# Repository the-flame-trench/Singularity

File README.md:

# Singularity On-board Computer
Singularity is a high-reliability focused on-board computer (OBC) for Pocketqube scale spacecraft.

It has been designed with a high degree of redundancy and fault tolerance in mind, and is compliant to ECSS-Q-ST-70-12C where possible.

# Design
The computer is based on the TI TMS570 family of safety critical microcontrollers, utilising dual lockstep ARM Cortex R4F CPU cores with extensive error checking capabilies.  

The rest of the board contains 8Mb external FRAM, 1Gb external bulk flash (both on their own single SPI bus), and a supervisor IC with RTC, watchdog and 256kb integrated FRAM (Issue_PROTO_A only).

Additionally, the board breaks out 3 CAN buses, with 1 designated for platform services, 1 for payload use, and a shared redundant bus.

As the Singularity OBC is being designed primarily for use in our TFTqube project, specific functions have been broken out to each connector, including a UART bus to a GPS module and a shared internal/external I2C bus.

The board is designed to be powered by a 3V3 external supply.  For maximum reliability, this supply should have some level of redundancy.  There is also a designated 5V input rail, although this is currently unused.

The board contains bulk decoupling for the main 3V3 rail, which is then distributed to various ICs.  The 3V3 rail is also fed through redundant TPS62850 switch mode power supplies, with outputs OR'd by an ideal diode controller and pair of MOSFETS, to provide a redundant 1V2 rail for the TMS570 core supply.

A version of the computer with 32MB SDRAM is under study, however at present, on an already dense 6 layer board, layout is infeasible.

# Usage
First, clone [TFT-KiCad-Source](https://github.com/the-flame-trench/TFT-KiCad-Source) and import all symbol and footprint libraries, found under /TFT_symbols and /TFT_footprints respectively, to your KiCad installation.  This MUST be done first, as the Singularity project references this library (as do other TFT projects).

Then, clone the Singularity repo, ensuring that your library tables are correctly set up with the TFT component libraries before opening the project.

# Contributing
The schematic and PCB are being designed in KiCad v6.0, and will move with the latest stable version.

We are working to bring every symbol and footprint into the TFT KiCad source libraries, however currently there are still a few instances using the default KiCad component library.

# Licence
Licenced under the [CERN OHLv2 - Strongly Reciprocal](LICENCE) or as referenced.

(c) The Flame Trench 2022

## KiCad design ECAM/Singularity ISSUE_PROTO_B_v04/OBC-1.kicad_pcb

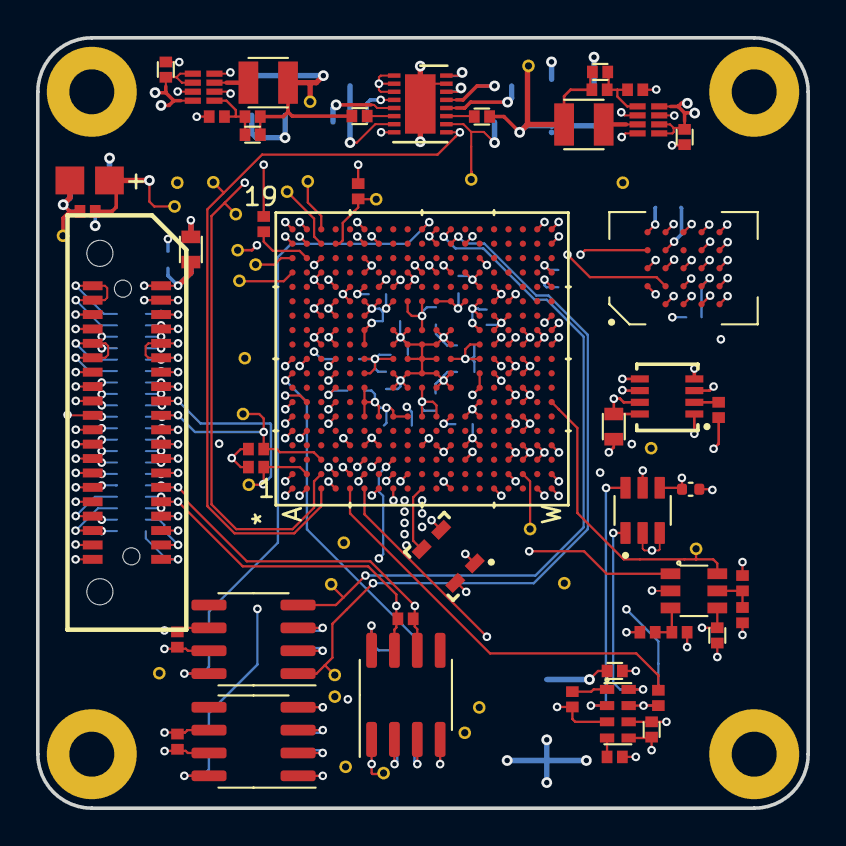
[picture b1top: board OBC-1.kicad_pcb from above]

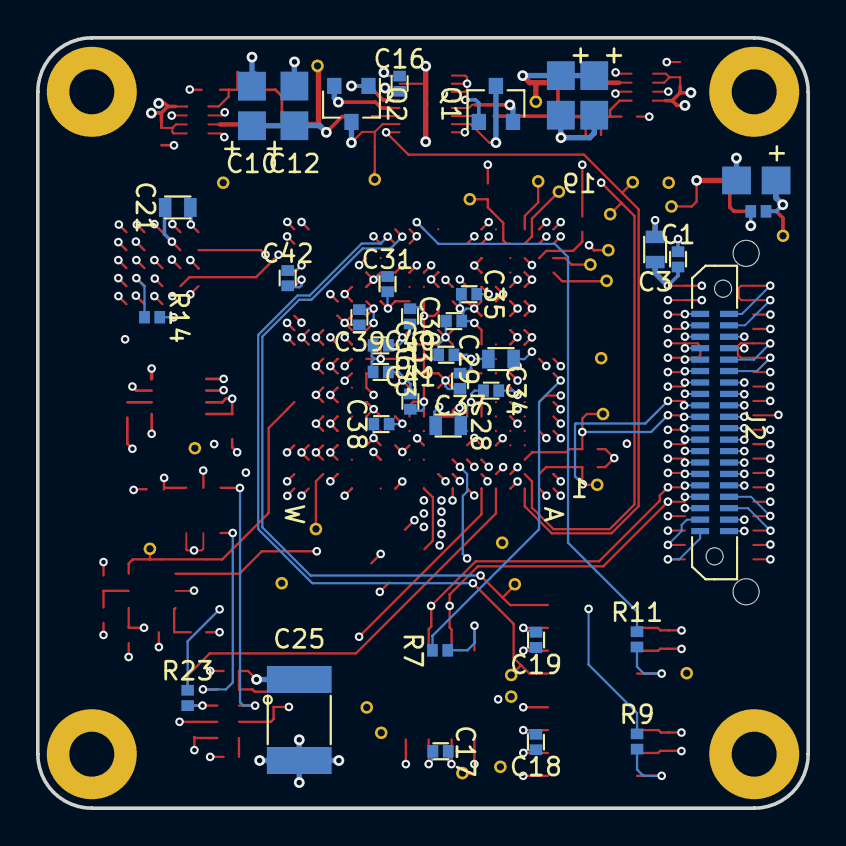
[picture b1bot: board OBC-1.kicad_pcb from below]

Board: 6 copper layers, 42.8 x 42.8 mm, 121 parts (37 on the bottom side), 76 nets.

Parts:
C1, C6, C7, C16, C17, C18, C19, C22, C23, C24, C30, C31, C32, C33, C34, C35, C36, C37, C38, C39, C40, C41, C42: 100n-10V-0402-5%-CER; 0402_CAP
C2, C3, C28, C29: 1u-10V-0603-10%-CER; 0603_CAP
C4, C5: 10u-10V-1206-10%-TANT; 1206_CAP_TANT
C8, C9: 10p-50V-0402-0.5p-CER; 0402_CAP
C10, C11, C12, C13: 10u-10V-0603-10%-CER; 1206_CAP_TANT
C14, C15: 56n-16V-0402-10%-CER; 0402_CAP
C20, C21: 100n-10V-0402-5%-CER; 0603_CAP
C25: 100uAH-1V8-4.4x3mm_LIon_batt; 1812_BATT
C26: 10n-10V-0402-5%-CER; C_0402_1005Metric
H1, H2, H3, H4: MountingHole_Pad; MountingHole_2.5mm_Pad
J1: ERM8-020-X; ERM8-020-XX.X-X-DV
J2: ERF6-020-X; ERF6-020-XX.X-X-DV-A-XX-K
L1, L2: 470nH-4A-20%; 2.5x2mm_I_SMD
Q1, Q2: MGSF1N02L; SOT-23
R1, R2: 100K-50V-0402-1%; 0402_RES
R3, R5: 16K2-50V-0402-1%; 0402_RES
R4, R6: 15K-50V-0402-1%; 0402_RES
R7, R9, R11, R25, R26: 10K-50V-0402-1%; 0402_RES
R8, R10, R12: 120R-50V-0402-1%; 0402_RES
R13, R14: 39R0-50V-0402-1%; 0402_RES
R15, R16, R21, R22, R23, R24: 0R-50V-0402; 0402_RES
R17, R18, R19, R20: 4K7-50V-0402-1%; 0402_RES
TP1, TP2, TP3, TP4, TP5, TP6, TP7, TP8, TP9, TP10, TP11, TP12, TP13, TP14, TP15, TP16, TP17, TP18, TP19, TP20, TP21, TP22, TP23, TP24, TP25, TP26, TP27, TP28, TP29, TP36, TP37: TEST-POINT; TP_0.4mmholesize_0.3mmring
U1, U2: TPS62850x-Q1; SOT-583
U3: LTC4353; DFN-16-1EP_3x4mm_P0.45mm_EP1.7x3.3mm
U4, U5, U6: SN65HVD230M-EP; SOIC-8_3.9x4.9mm_P1.27mm
U7: CY15B108QI
U8: S70FL01GS; BGA-24_5x5_6.0x8.0mm
U9: TPS3813K33-EP; SOT-236
U10: RV-3032-C7
U11: TMS5701227CZWTQQ1; ZWT337
U12: TMP100; SOT-23
X2: LFTCXO075797

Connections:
/CAN_XCVR_PL/CAN_H_PL: J1.16, R8.1, U4.7
/CAN_XCVR_PL/CAN_L_PL: J1.15, R8.2, U4.6
/CAN_XCVR_PL/CAN_PL_D: TP22.1, U4.1, U11.A10
/CAN_XCVR_PL/CAN_PL_R: TP24.1, U4.4, U11.B10
/CAN_XCVR_PL/CAN_PL_Rs: R7.1, U11.A9
/CAN_XCVR_R/CAN_H_PL: J1.19, J2.19, R10.1, U5.7
/CAN_XCVR_R/CAN_L_PL: J1.20, J2.20, R10.2, U5.6
/CAN_XCVR_R/CAN_PL_D: TP21.1, U5.1, U11.H2
/CAN_XCVR_R/CAN_PL_R: TP20.1, U5.4, U11.H1
/CAN_XCVR_R/CAN_PL_Rs: R9.1, U11.G1
/Connectors/ADS_nRST: J1.11, U11.M1
/Connectors/CAN_H_PA: J1.24, J2.24, R12.1, U6.7
/Connectors/CAN_L_PA: J1.23, J2.23, R12.2, U6.6
/Connectors/GPS_P1PPS: J1.29, U11.A6
/Connectors/GPS_RXD0: J1.31, U11.B7
/Connectors/GPS_STS: J1.28, U11.A5
/Connectors/GPS_TXD0: J1.32, U11.A7
/Connectors/GPS_nRST: J1.30, U11.B5
/FL_1/FL_1_CLK: U8.B2, U11.F18
/FL_1/FL_1_SI_IO0: U8.D3, U11.F19
/FL_1/FL_1_SO_IO1: R14.1, U11.G18
/FL_1/FL_1_nCS1: U8.C2, U11.F3
/FL_1/FL_1_nCS2: U8.A3, U11.G3
/FL_1/FL_1_nHOLD_IO3: U8.D4, U11.H3
/FL_1/FL_1_nRESET: U8.A4, U11.F2
/FRAM_1/FRAM_1_CIPO: R13.1, U11.D2
/FRAM_1/FRAM_1_CLK: U7.6, U11.E2
/FRAM_1/FRAM_1_COPI: U7.5, U11.D1
/FRAM_1/FRAM_1_nCS: U7.1, U11.N3
/Power/GATE_1: Q2.2, U3.12
/Power/GATE_2: Q1.2, U3.5
/Power/OBC_1V25_P_PG: TP36.1, U3.9, U11.C1
/Power/OBC_1V25_R_PG: TP37.1, U3.8, U11.C2
/RTC/OBC_I2C_SCL: J1.10, R20.2, TP29.1, U10.8, U11.C3, U12.1
/RTC/OBC_I2C_SDA: J1.9, R19.2, TP28.1, U10.2, U11.B2, U12.6
/RTC/RTC_CLKOUT: R23.2, R24.2, U10.7
/RTC/RTC_nINT: R26.2, U10.3, U11.F1
/Supervisor/SPVSR_PET: U9.1, U11.J2
/Supervisor/SPVSR_nRST: TP27.1, U9.6, U11.W7
/Supervisor/WDR: R21.2, R22.1, U9.5
/Supervisor/WDT: R15.2, R16.1, U9.3
/TMS570_uC/CAN_PA_D: TP25.1, U6.1, U11.M18
/TMS570_uC/CAN_PA_R: TP23.1, U6.4, U11.M19
/TMS570_uC/CAN_PA_Rs: R11.1, U11.K19
/TMS570_uC/JTAG_RTCK: TP1.1, U11.A16
/TMS570_uC/JTAG_TCK: TP5.1, U11.B18
/TMS570_uC/JTAG_TDI: TP2.1, U11.A17
/TMS570_uC/JTAG_TDO: TP6.1, U11.C18
/TMS570_uC/JTAG_TEST: TP3.1, U11.U2
/TMS570_uC/JTAG_TMS: TP7.1, U11.C19
/TMS570_uC/JTAG_nTRST: R17.1, TP4.1, U11.D18
/TMS570_uC/uC_OSC_IN: U11.K1, X2.3
/TMS570_uC/uC_nRST: R18.1, U11.B17
GND: C1.2, C2.2, C3.2, C5.2, C6.2, C7.2, C10.2, C11.2, C12.2, C13.2, C16.2, C17.2, C18.2, C19.2, C20.2, C21.2, C22.2, C23.2, C24.2, C25.2, C26.2, C28.2, C29.2, C30.2, C31.2, C32.2, C33.2, C34.2, C35.2, C36.2, C37.2, C38.2, C39.2, C40.2, C41.2, C42.2, H1.1, H2.1, H3.1, H4.1, J1.3, J1.4, J1.5, J1.6, J1.7, J1.8, J1.12, J1.13, J1.14, J1.17, J1.18, J1.21, J1.22, J1.25, J1.26, J1.27, J1.33, J1.34, J1.37, J1.38, J2.1, J2.2, J2.3, J2.4, J2.5, J2.6, J2.7, J2.8, J2.9, J2.10, J2.11, J2.12, J2.13, J2.14, J2.15, J2.16, J2.17, J2.18, J2.21, J2.22, J2.25, J2.26, J2.27, J2.28, J2.29, J2.30, J2.31, J2.32, J2.33, J2.34, J2.37, J2.38, R2.2, R4.2, R6.2, R16.2, R22.2, TP8.1, TP9.1, TP10.1, TP11.1, TP12.1, TP13.1, TP14.1, TP15.1, U1.3, U1.6, U1.8, U2.3, U2.6, U2.8, U3.1, U3.2, U3.3, U3.15, U3.16, U3.17, U4.2, U5.2, U6.2, U7.4, U8.A2, U8.A5, U8.B1, U8.B3, U8.B5, U8.C1, U8.C3, U8.C5, U8.D1, U8.D5, U8.E1, U8.E2, U8.E3, U8.E4, U8.E5, U9.2, U10.5, U11.A1, U11.A2, U11.A18, U11.A19, U11.B1, U11.B19, U11.C11, U11.C12, U11.C13, U11.C14, U11.C15, U11.C16, U11.C17, U11.D6, U11.D7, U11.D8, U11.D9, U11.D10, U11.D11, U11.D12, U11.D13, U11.D14, U11.D15, U11.E4, U11.E14, U11.E15, U11.F4, U11.F15, U11.F16, U11.F17, U11.G4, U11.G15, U11.H8, U11.H9, U11.H11, U11.H12, U11.H15, U11.J8, U11.J9, U11.J10, U11.J11, U11.J12, U11.J15, U11.J16, U11.K4, U11.K9, U11.K10, U11.K11, U11.K16, U11.L4, U11.L8, U11.L9, U11.L10, U11.L11, U11.L12, U11.L16, U11.L18, U11.L19, U11.M4, U11.M8, U11.M9, U11.M11, U11.M12, U11.M16, U11.N4, U11.N16, U11.N18, U11.P4, U11.P15, U11.P16, U11.P17, U11.R1, U11.R10, U11.R11, U11.R12, U11.R13, U11.R14, U11.R15, U11.T2, U11.T3, U11.T4, U11.T5, U11.T6, U11.T7, U11.T8, U11.T9, U11.T10, U11.T11, U11.T13, U11.T14, U11.U3, U11.U4, U11.U5, U11.U6, U11.U7, U11.U8, U11.U9, U11.U10, U11.U11, U11.U12, U11.V1, U11.V3, U11.V4, U11.V11, U11.V12, U11.V19, U11.W1, U11.W2, U11.W4, U11.W11, U11.W12, U11.W13, U11.W16, U11.W18, U11.W19, U12.2, U12.3, U12.5, X2.1, X2.2
unnamed: C4.2, C5.1, R1.2, R2.1, TP16.1
unnamed: C8.2, R3.2, R4.1, U1.5
unnamed: C9.2, R5.2, R6.1, U2.5
unnamed: C14.2, U3.6
unnamed: C15.2, U3.11
unnamed: L1.1, U1.7
unnamed: L2.1, U2.7
unnamed: R7.2, U4.8
unnamed: R9.2, U5.8
unnamed: R11.2, U6.8
unnamed: R13.2, U7.2
unnamed: R14.2, U8.D2
unnamed: R23.1, U11.R9
unnamed: R24.1, U11.E1
unnamed: R25.2, U10.4
OBC_1V25: C29.1, C32.1, C33.1, C36.1, C37.1, C40.1, C41.1, Q1.3, Q2.3, TP19.1, U3.7, U3.10, U11.F9, U11.F10, U11.H10, U11.J14, U11.K6, U11.K8, U11.K12, U11.K14, U11.L6, U11.M10, U11.P10, U11.P11
OBC_1V25_P: C8.1, C10.1, C12.1, C15.1, L1.2, Q2.1, R3.1, TP17.1, U3.13
OBC_1V25_R: C9.1, C11.1, C13.1, C14.1, L2.2, Q1.1, R5.1, TP18.1, U3.4
OBC_3V3: C1.1, C2.1, C3.1, C4.1, C6.1, C7.1, C16.1, C17.1, C18.1, C19.1, C20.1, C21.1, C22.1, C23.1, C26.1, C28.1, C30.1, C31.1, C34.1, C35.1, C38.1, C39.1, C42.1, J1.1, J1.2, R1.1, R15.1, R17.2, R18.2, R19.1, R20.1, R21.1, R25.1, TP26.1, U1.1, U1.2, U1.4, U2.1, U2.2, U2.4, U3.14, U4.3, U5.3, U6.3, U7.3, U7.7, U7.8, U8.B4, U9.4, U10.6, U11.F6, U11.F7, U11.F8, U11.F11, U11.F12, U11.F13, U11.F14, U11.G6, U11.G14, U11.H6, U11.H14, U11.J6, U11.L14, U11.M6, U11.M14, U11.N6, U11.N14, U11.P6, U11.P7, U11.P8, U11.P9, U11.P12, U11.P13, U11.P14, U11.W15, U12.4, X2.4
OBC_RTC_Vbackup: C24.1, C25.1, R26.1, U10.1
PAYLOAD_3V3: J1.35, J1.36, J2.35, J2.36
PAYLOAD_5V: J1.39, J1.40, J2.39, J2.40

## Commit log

2021-03-12 First commit to online source, schematic status ISSUE_PROTO_A ready for footprint and PCB dev
2021-03-12 Updated README, LICENCE
2021-03-24 Minor schematic information updates
2021-03-24 added PCB outline, fixed some mispositioning in the schematic, removed incorrect footprint assignment from U7
2021-03-24 addded prelim HTML BoM files
2021-03-28 corrected labelling issue on top level schematic
2021-03-29 set up PCB stackup and routing design rules, began power planing and power breakouts for the TMS570
2021-03-30 added extra decoupling cap for VCCAD and completed initial routing of TMS570 power breakout and decoupling
2021-03-30 replaced power ORing MOSFETs with lower Rds SOT-23 package
2021-03-30 save cleanup
2021-03-30 Add power budget spreadsheet
2021-03-30 schematic updated with new power symbols for OBC_1V25
2021-03-30 changed resistor dividers in the power section to supply 1.25V to TMS570 core
2021-03-30 Add more calculations to power budget
2021-03-31 annoted new regulator Vout set resistors
2021-03-31 assigned testpoint and ERF6 footprints
2021-03-31 corrected heirarchical label naming after 1.25v power change
2021-03-31 added new footprints to layout in prep for locating connector positions
2021-03-31 finalised connector position, updated testpoint footprint assingment. SMPS footprint netlist has a bug that will hopefully be fixed when it has a valid footprint
2021-03-31 fixed incorrect footprint assignment to U1 and U2
2021-03-31 connectors broken out
2021-03-31 updates to CAN power trace routing and initial CAN differential rail routing
2021-04-01 signals broken out from TMS570
2021-04-01 added board level bulk decoupling
2021-04-01 first power supply laid out
2021-04-01 updated passive footprints, fixed errors, re-laid out CAN xcvrs
2021-04-01 initial layout of 2nd power supply done, 3V3 plane routing to the supply inputs needs work, currently too broken up by ground vias
2021-04-01 added testpoints to 2nd supply, positioned early floorplan for ORing diode controller, needs work - gates are on wrong sides - need to switch supply sides
2021-04-01 cleanup save of sch
2021-04-01 updated CAN xcvr positions
2021-04-01 fixed wonky payload CAN bus routing
2021-04-02 progressed power supply layout, added 3D models to footprints
2021-04-02 updated power planes
2021-04-02 initial supervisor layout, needs XTAL adding
2021-04-02 completed supervisor layout
2021-04-02 initial SDRAM positioning, need to floorplan remainder of memory ICs
2021-04-02 fixed bus netlisting issue - labelling was incorrectly formatted
2021-04-02 removed SDRAM to simplify initial design
2021-04-02 corrected typos in README
2021-04-02 fixed typo in GPS net label
2021-04-02 fixed typo in README, added flash chip for floorplanning, added JTAG testpoints for pogo pinning
2021-04-02 initial routing of flash chip
2021-04-02 updated flash chip breakout and bus routing to neaten and simplify, keeping to one layer
2021-04-02 added pullup resistors for I2C, reset, etc. routed PG lines
2021-04-02 rerouted some power to make routing supervisor comms bus easier
2021-04-02 routed supervisor SPI and IO ports
2021-04-02 fixed 3V3 plane vertex
2021-04-02 payload CAN bus routed
2021-04-03 moved some of the TMS570 grounding vias to make room for updated 1V25 power plane
2021-04-03 further prep for TMS570 power plane routing
2021-04-03 added new power planes for TMS570
2021-04-03 power plane adjustments
2021-04-03 more plane adjustments
2021-04-03 CAN buses routed
2021-04-03 temporarily made all connector grounding vias blind to only one ground plane, will revert some once connector is fully broken out and routed to keep local plane balance
2021-04-03 GPS UART and IO routed to connector
2021-04-03 increased signal separation of power-good traces from I2C section
2021-04-03 fixed unnecessary trace necking under BGA component
2021-04-07 updated BoM
2021-05-08 Updated KiCAD to 5.1.10 and restructured repo files
2021-05-08 renamed dir
2021-05-24 updated schematic with FRAM footprint link
2021-05-24 added FRAM to PCB layout
2021-05-24 added ground test points, adjusted trace width on RTC XTAL
2021-05-24 updated FRAM_CLK routing
2021-05-24 updated uC XTAL footprint assignment
2021-05-24 added uC XTAL, routed ground stitching and power plane
2021-05-24 updated schematic with release date, plotted updated pdf
2021-05-24 updated README to emphasise IC supervisor with integrated FRAM is Issue A only
2021-05-24 added new supervisor circuit to schematic
2021-05-24 added RTC schematic, fixed ADS_nRST pin not driven by TMS570
2021-05-24 fixed ADS_nRST pin not driven
2021-05-24 revised schematic to PROTO_A_v02
2021-05-24 plotted initial schematic PDF
2021-05-24 file catchup - RTCv2.sch and ISSUE_PROTO_B pdfs
2021-05-24 plotted issue proto_A_v02 schematic pdf
2021-05-24 updated PCB layout for Issue B supervisor/RTC circuitry
2021-05-24 file cleanup
2021-05-24 updated Issue_proto_B schematic plot
2021-05-29 initial commit, power test points linked to heirarchy
2021-05-29 set up test points for TSM570 schematic
2021-05-29 cleaned up modules with no current testpoints
2021-05-29 updated RFC connector on BoN to ERF8 for bottom layer mounting
2021-06-03 file cleanup, .attributes update
2021-06-04 updated README to reflect Issue_PROTO_A's old RTC/supervisor architecture
2021-06-05 Fix power budget math
2021-06-05 saving out files
2021-06-05 plotted early v001 schematic (incomplete)
2021-06-05 added OBC_1V25_P/R_PG net test points, updated TP ref des
2021-06-05 added Power Good testpoints to 1V25_P/R_PG rails, removed unnecessary TP35 from power schematic
2021-06-05 updated title blocks and testpoint/connector passthroughs
2021-06-05 updated text labelling
2021-06-05 updating PCB with current proto_B test point locations
2021-06-05 further PCB update to locate test points with current issue B PCB
2021-06-05 updated schematic dates and titles
2021-06-05 plotted issue_Proto_B_v02 schematic
2021-06-05 updated TP35 to TP19 to match base computer refdes in BoN
2021-06-05 plotted v002 of Issue_proto_B BoN
2022-03-19 closing merge
2022-06-04 migrated to KiCAD v6. For now, old v5 files remain as legacy. Please only use v6 from now on
2022-06-04 updated BoN directory to KiCAD v6
2022-06-04 updated .gitignore to ignore v5 .sch files
2022-06-04 added PCB from most up to date IssB_v04, needs components removing and TP refdes checking as in Issue27

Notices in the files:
parts and their libraries:
Copyright 2016 Accelerated Designs. All rights reserved.
